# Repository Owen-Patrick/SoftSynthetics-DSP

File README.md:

# Soft Synthetics DSP Adapator
This Repository Contains hardware for adapting a cheap Karaoke DSP board to eurorack.

It turns one of these:

into an 10HP eurorack stereo multi-effects module with some fun clock modulation voltage control:

## What's provided
This repository contains:
* Kicad Circuit layout
* Kicad PCB and panel layouts
* Gerbers for the panel and circuit boards

## Learn More
More information is avaialbe here: 

## Caveats
v1.1 This is an untested revision of the original board which had some clearance issues. I believe they have been rectified but please do double check! I have not printed it because v1.0 did work with plenty of bodging which I do not recommend.

THe clock modulator circuit requires a fairly simple modifaction to the board in order to override the clock input (x). All you have to do is remove the crystal and replace with in a header to connect "x" instead, which is a new clock siglan being generated by the pt2399. From what I can tell, the frequency of the DSP boards clock changes between manufacturers so experimentation to find the ideal frequency and modulation amount. If that doesn't excite then you could just modify the PCB layout and remove that whole part of the circuit from the PCB and front panel. 

It's also not the prettiest in constuction and requires some pretty cosy bends of the cables that connect the DSP boards display and main board (i've seen some folk replace that cable with softer wires). The final consution is as so:

*the display board attaches to the main back board of via 2 M3 stadnoffs.
*That display board connects to the interface with an m3 standoff and 2.54mm pin headers. 
*The DSP processor board mounts to the interface.
*The cables fit together that way you'd expect: x to the clock in, in, Lout, Rout to the DSP PCB, and 5v to power in of the DSP. 

If I have time i'll make a little diagram at some point! until then it mostly makes sense.

## Mentions 
This project is a culmination of various other creators work into one package which shares the benefits they each brung to the table. Those insanley talented peaople are:

* - 
        I adopted the wonderfully creative clock control using a PT2399 chip.
*Jos from LMNC forums - 
*I took inspiration from single gang pot Wet/Dry mixer used in this scehmatic
    Hagiwo - 
    Hagiwo is a powerhouse in making lovely, innovative, and accessable DIY modules. They put me onto this device in the first place

## License 
CC BY-SA 4.0
which . AKA be nice :)

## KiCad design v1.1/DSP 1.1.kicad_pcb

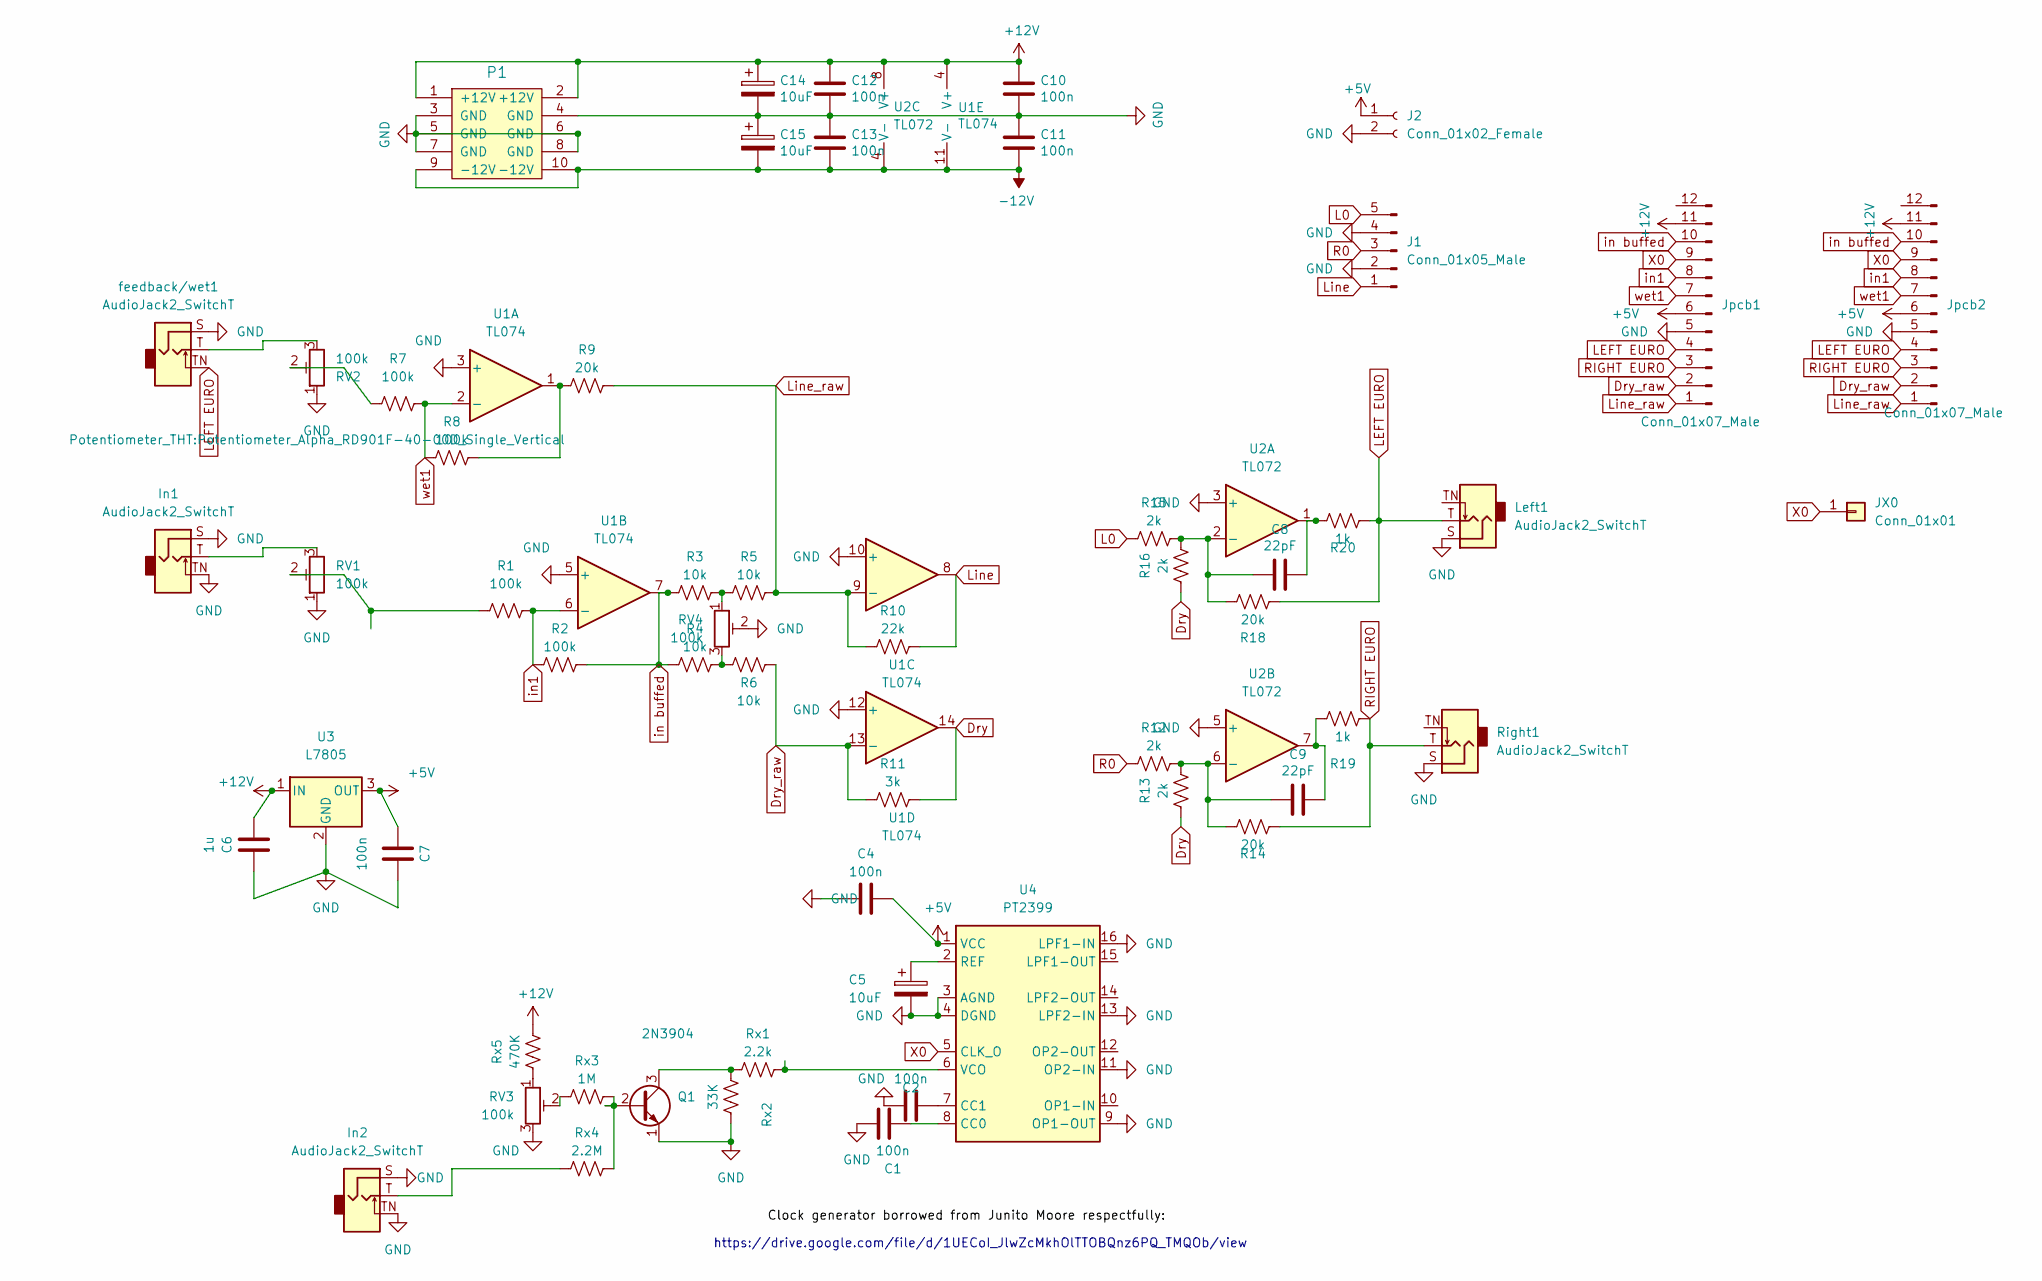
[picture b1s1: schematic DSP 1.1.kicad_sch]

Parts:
C1, C2, C4, C7: 100n; C_Axial_L5.1mm_D3.1mm_P10.00mm_Horizontal
C5: 10uF; CP_Radial_D6.3mm_P2.50mm
C6: 1u; C_Axial_L5.1mm_D3.1mm_P10.00mm_Horizontal
C8, C9: 22pF; C_Disc_D7.5mm_W2.5mm_P5.00mm
C10, C11: 100n; C_Disc_D7.5mm_W2.5mm_P5.00mm
C12, C13: 100n; C_0805_2012Metric_Pad1.15x1.40mm_HandSolder
C14, C15: 10uF; CP_Radial_D5.0mm_P2.50mm
In1, In2: AudioJack2_SwitchT; Jack_3.5mm_QingPu_WQP-PJ398SM_Vertical_CircularHoles
J1: Conn_01x05_Male; PinHeader_1x05_P2.54mm_Vertical
J2: Conn_01x02_Female; PinHeader_1x02_P2.54mm_Vertical
JX0: Conn_01x01; PinHeader_1x01_P2.54mm_Vertical
Jpcb1, Jpcb2: Conn_01x07_Male; PinHeader_2x06_P2.54mm_Vertical
Left1: AudioJack2_SwitchT; Jack_3.5mm_QingPu_WQP-PJ398SM_Vertical_CircularHoles
P1: EURO_PWR_2x5; IDC-2x5
Q1: 2N3904; TO-92_Inline
R1, R2, R7, R8: 100k; R_Axial_DIN0207_L6.3mm_D2.5mm_P10.16mm_Horizontal
R3, R4, R5, R6: 10k; R_Axial_DIN0207_L6.3mm_D2.5mm_P10.16mm_Horizontal
R9, R14, R18: 20k; R_Axial_DIN0207_L6.3mm_D2.5mm_P10.16mm_Horizontal
R10: 22k; R_Axial_DIN0207_L6.3mm_D2.5mm_P10.16mm_Horizontal
R11: 3k; R_Axial_DIN0207_L6.3mm_D2.5mm_P10.16mm_Horizontal
R12, R13, R15, R16: 2k; R_Axial_DIN0207_L6.3mm_D2.5mm_P10.16mm_Horizontal
R19, R20: 1k; R_Axial_DIN0207_L6.3mm_D2.5mm_P10.16mm_Horizontal
RV1, RV2, RV3, RV4: 100k; Potentiometer_Alpha_RD901F-40-00D_Single_Vertical
Right1: AudioJack2_SwitchT; Jack_3.5mm_QingPu_WQP-PJ398SM_Vertical_CircularHoles
Rx1: 2.2k; R_Axial_DIN0207_L6.3mm_D2.5mm_P10.16mm_Horizontal
Rx2: 33K; R_Axial_DIN0207_L6.3mm_D2.5mm_P10.16mm_Horizontal
Rx3: 1M; R_Axial_DIN0207_L6.3mm_D2.5mm_P10.16mm_Horizontal
Rx4: 2.2M; R_Axial_DIN0207_L6.3mm_D2.5mm_P10.16mm_Horizontal
Rx5: 470K; R_Axial_DIN0207_L6.3mm_D2.5mm_P10.16mm_Horizontal
U1: TL074; DIP-14_W7.62mm_LongPads
U2: TL072; DIP-8_W7.62mm_LongPads
U3: L7805; TO-220-3_Horizontal_TabDown
U4: PT2399; DIP-16_W7.62mm_LongPads
feedback/wet1: AudioJack2_SwitchT; Jack_3.5mm_QingPu_WQP-PJ398SM_Vertical_CircularHoles

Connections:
+5V: C4.2, C7.2, J2.1, Jpcb1.6, Jpcb2.6, U3.3 (OUT), U4.1 (VCC)
+12V: C6.2, C10.2, C12.2, C14.1, Jpcb1.11, Jpcb2.11, P1.1 (+12V), P1.2 (+12V), Rx5.2, U1.4 (V+), U2.8 (V+), U3.1 (IN)
-12V: C11.1, C13.1, C15.2, P1.9 (-12V), P1.10 (-12V), U1.11 (V-), U2.4 (V-)
Dry: R11.2, R13.1, R16.1, U1.14
Dry_raw: Jpcb1.2, Jpcb2.2, R6.2, R11.1, U1.13 (-)
GND: C1.1, C2.1, C4.1, C5.2, C6.1, C7.1, C10.1, C11.2, C12.1, C13.2, C14.2, C15.1, In1.S, In1.TN, In2.S, In2.TN, J1.2, J1.4, J2.2, Jpcb1.5, Jpcb2.5, Left1.S, P1.3 (GND), P1.4 (GND), P1.5 (GND), P1.6 (GND), P1.7 (GND), P1.8 (GND), Q1.1 (E), RV1.1, RV2.1, RV3.3, RV4.2, Right1.S, Rx2.1, U1.3 (+), U1.5 (+), U1.10 (+), U1.12 (+), U2.3 (+), U2.5 (+), U3.2 (GND), U4.3 (AGND), U4.4 (DGND), U4.9 (OP1-OUT), U4.11 (OP2-IN), U4.13 (LPF2-IN), U4.16 (LPF1-IN), feedback/wet1.S
L0: J1.5, R15.1
LEFT EURO: Jpcb1.4, Jpcb2.4, Left1.T, R18.1, R20.1, feedback/wet1.TN
Line: J1.1, R10.2, U1.8
Line_raw: Jpcb1.1, Jpcb2.1, R5.2, R9.2, R10.1, U1.9 (-)
unnamed: C1.2, U4.8 (CC0)
unnamed: C2.2, U4.7 (CC1)
unnamed: C5.1, U4.2 (REF)
unnamed: C8.1, R15.2, R16.2, R18.2, U2.2 (-)
unnamed: C8.2, R20.2, U2.1
unnamed: C9.1, R12.2, R13.2, R14.2, U2.6 (-)
unnamed: C9.2, R19.2, U2.7
unnamed: In1.T, RV1.3
unnamed: In2.T, Rx4.1
unnamed: Q1.2 (B), Rx3.2, Rx4.2
unnamed: Q1.3 (C), Rx1.1, Rx2.2
unnamed: R1.1, RV1.2
unnamed: R3.2, R5.1, RV4.1
unnamed: R4.2, R6.1, RV4.3
unnamed: R7.1, RV2.2
unnamed: R8.2, R9.1, U1.1
unnamed: RV2.3, feedback/wet1.T
unnamed: RV3.1, Rx5.1
unnamed: Rx1.2, U4.6 (VCO)
R0: J1.3, R12.1
RIGHT EURO: Jpcb1.3, Jpcb2.3, R14.1, R19.1, Right1.T
X0: JX0.1, Jpcb1.9, Jpcb2.9, U4.5 (CLK_O)
in1: Jpcb1.8, Jpcb2.8, R1.2, R2.1, U1.6 (-)
in buffed: Jpcb1.10, Jpcb2.10, R2.2, R3.1, R4.1, U1.7
wet1: Jpcb1.7, Jpcb2.7, R7.2, R8.1, U1.2 (-)

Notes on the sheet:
https://drive.google.com/file/d/1UECoI_JlwZcMkhOlTTOBQnz6PQ_TMQOb/view

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
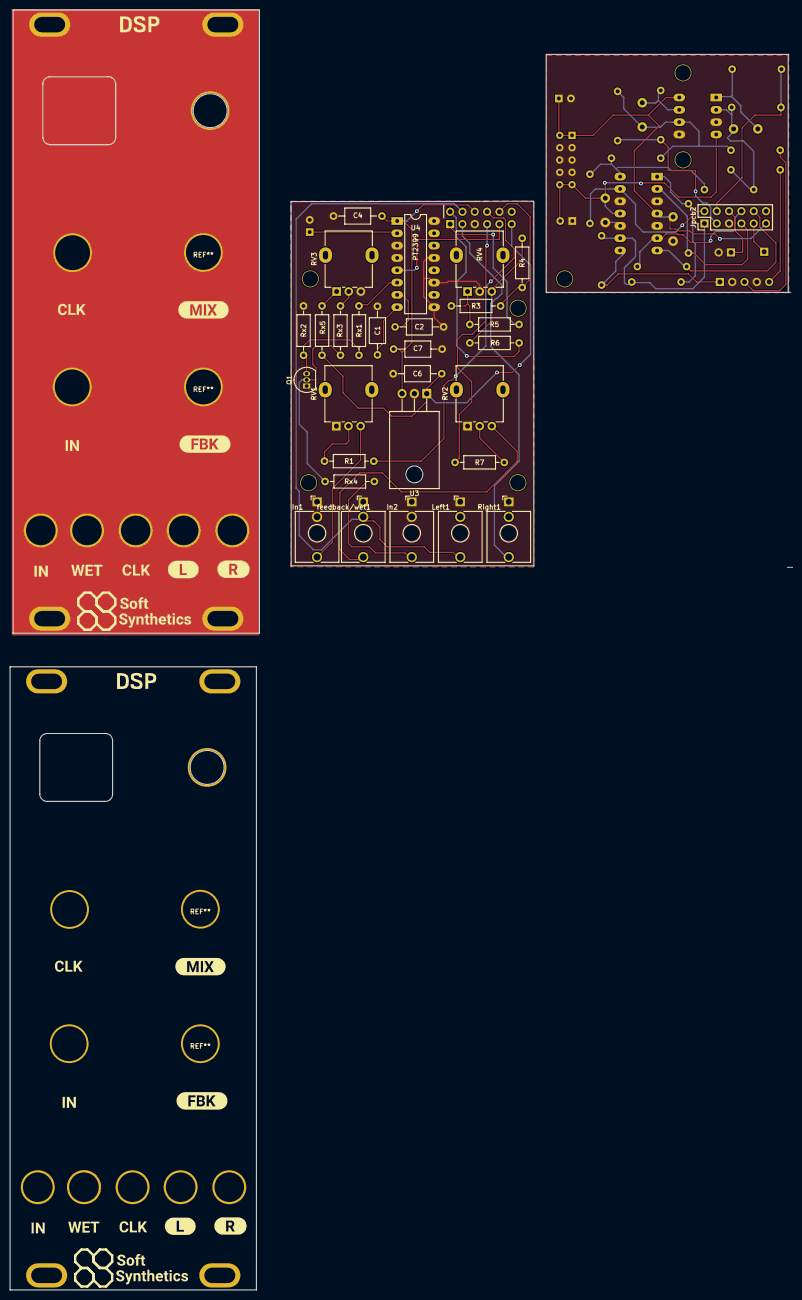
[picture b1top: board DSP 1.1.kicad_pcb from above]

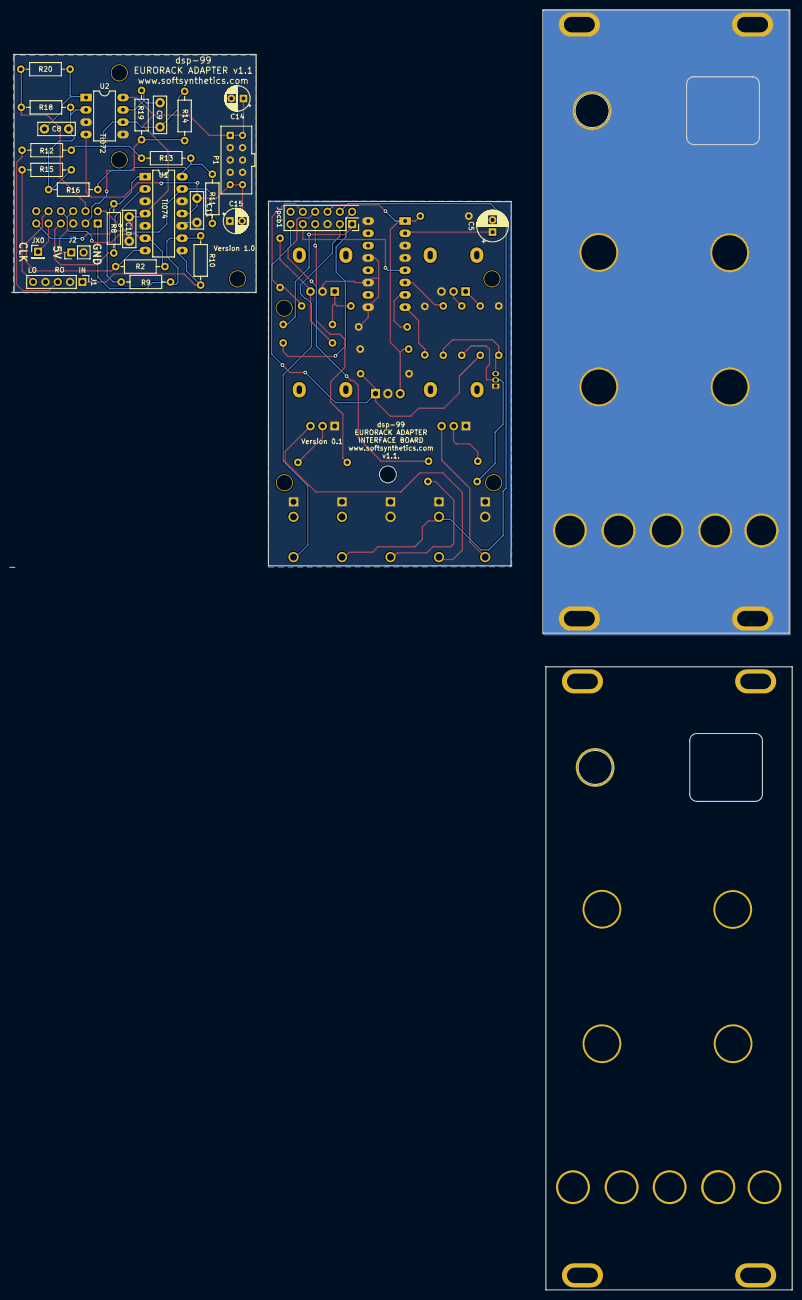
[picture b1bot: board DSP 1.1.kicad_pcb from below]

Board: 2 copper layers, 161.2 x 263.9 mm, 80 parts (26 on the bottom side), 35 nets.

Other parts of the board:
kibuzzard-64D80CCD, kibuzzard-64D80CCD#2: G***; kibuzzard-64D80CCD
kibuzzard-643BAF55, kibuzzard-643BAF55#2, kibuzzard-643BAF55#3, kibuzzard-643BAF55#4: G***; kibuzzard-643BAF55
kibuzzard-643BAFC1, kibuzzard-643BAFC1#2: G***; kibuzzard-643BAFC1
kibuzzard-643BAFCE, kibuzzard-643BAFCE#2, kibuzzard-643BAFCE#3, kibuzzard-643BAFCE#4: G***; kibuzzard-643BAFCE
kibuzzard-643BB3B1, kibuzzard-643BB3B1#2: G***; kibuzzard-643BB3B1
kibuzzard-643BB32E, kibuzzard-643BB32E#2: G***; kibuzzard-643BB32E
kibuzzard-643BB339, kibuzzard-643BB339#2: G***; kibuzzard-643BB339
kibuzzard-643BB390, kibuzzard-643BB390#2: G***; kibuzzard-643BB390
kibuzzard-644033EB, kibuzzard-644033EB#2: G***; kibuzzard-644033EB
kibuzzard-644033FD, kibuzzard-644033FD#2: G***; kibuzzard-644033FD

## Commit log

2023-10-15 Update README.md
    First Draft
2023-10-15 Updated Readme, add v1.1 files
2023-10-15 V1.1
